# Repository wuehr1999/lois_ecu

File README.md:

# lois_ecu
This repository contains the [hardware](https://github.com/wuehr1999/lois_ecu/tree/main/hw), [firmware](https://github.com/wuehr1999/lois_ecu/tree/main/firmware) and [tooling](https://github.com/wuehr1999/lois_ecu/tree/main/rpmctrl_tuning) for a general purpose control unit for differential drive based wheeled robotics platforms. An image of the real hardware and a component diagram are shown below.

## Firmware

The [firmware](https://github.com/wuehr1999/lois_ecu/tree/main/firmware/loisECU) comes as a STM32 CubeIDE project and currently implements the following features:

- Closed single loop RPM-control for two DC-motors with encoders
- Realtime calculation of differential drive odometry
- Servo sweep for the [ball distribution device](https://github.com/generationmake/BDD)
- NMEA parser on RS232_1 (used for UBLOX GPS)
- NMEA parser on RS232_2 (used for KVH-C100 fluxgate compass)
- Host communication via UART
- 2048 Byte reealtime reord buffer ( recording of RPM, torque and compass heading over a given time )
- Easy human readable and debuggable ASCII communication leaned on modbus protocol with optional checksum

### Host communication protocol

The communication protocol is ASCII-based and the messages have the following format:

```:<8-bit command><32-bit payload><8-bit crc><\n>```

All values are written in hexadecimal, so that every message has a fixed length of 14 characters. There is also a [ROS2 driver](https://github.com/wuehr1999/lois_ecu_ros), which uses the given protocol to make the functionalities available via ROS.

The table below shows the currently implemented messages. There are also some periodic messages from the ECU to the Host. By writing the commands of this messages to the ECU, the period can be changed. The payload is then interpreted as an ```uint16``` containing the period time in milliseconds. ```0xfffe``` then means requesting a periodic message once and ```0xffff``` turns the message off completely.

| Command | Function | To ECU (E)/ To Host (H) | Payload interpretation | Periodic |
| - | - | - | - | - |
| ```0x01``` | Dutycycle of left and right motor, RPM controller gets disabled | E | ```2 x int16``` ( -100 % - 100 %)  | |
| ```0x02``` | RPM of left and right motor, RPM controller gets enabled | E | ```2 x int16``` | |
| ```0x03```  | Turn board LED on or off | E | ```bool``` | |
| ```0x04``` | Record a given amount of RPM samples | E / H | ```2 x uint16``` ( m samples left and n right ) to ECU or sequential max(m, n) ``` 2 x uint16``` ( tick timestamps in 100 ns followed by ```0x00000000``` ) to Host |  |
| ```0x05``` | Emergency stop button pressed | H | ```bool``` |  |
| ```0x06``` | Kp left controller | E | ```float32``` |  |
| ```0x07``` | Tn left controller | E | ```float32``` |  |
| ```0x08``` | Td left controller | E | ```float32``` |  |
| ```0x09``` | Kp right controller | E | ```float32``` |  |
| ```0x0a``` | Tn right controller | E | ```float32``` |  |
| ```0x0b``` | Td right controller | E | ```float32``` |  |
| ```0x0c``` | Record a given amount of compass heading samples | E | ```uint32```  n samples to ECU or sequential n + 1 ```2 x int16``` ( heading data in degrees ) followed by ```0x016A016A``` to Host |  |
| ```0x0d``` | GPS position | E / H | 3 sequential ```uint32, 2 x float32``` ( ```0xffffffff```, latitude, longitude ) | x |
| ```0x0e``` | GPS time | E / H | ```3 x uint8``` ( hours, minutes, seconds ) | x |
| ```0x0f``` | GPS date | E / H | ```3 x uint8``` ( year, month, day ) | x |
| ```0x10``` | Compass heading | E / H | ```1 x int16``` ( degrees to north ) | x |
| ```0x11``` | Terminal mode ( forward serial sensor Rx input on this interface ) | E | ```uint8``` ( Host protocol, GPS sensor, compass sensor ) | |
| ```0x12``` | Encoder overall ticks | E / H | 4 sequential ```4 x uint32``` ( ```0xffffffff```, timestamp in nanoseconds, left encoder, right encoder )  | x |
| ```0x13``` | Left encoder short level time correction | E | ```float32``` |  |
| ```0x14``` | Left encoder long level time correction | E | ```float32``` |  |
| ```0x15``` | Right encoder short level time correction | E | ```float32``` |  |
| ```0x16``` | Right encoder long level time correction | E | ```float32``` |  |
| ```0x17``` | Record a given amount of Torque samples | E / H | ```2 x uint16``` ( m samples left and n right ) to ECU or sequential max(m, n) ``` 2 x uint16``` ( torque 12-bit ADC values followed by ```0x00000000``` ) to Host |  |
| ```0x18``` | Reset all controllers, interfaces and counters | E  | - |  |
| ```0x19``` | Use ball distribution device once | E | - |  |
| ```0x20``` | Odometry calculated on robot | E / H | sequential 7 started with ```0xffffffff``` followed by ```6 x float32``` ( x, y, phi, dx, dy, dphi ) | x |

## Encoder and RPM controller tuning

There is [tooling in Scilab](https://github.com/wuehr1999/lois_ecu/tree/main/rpmctrl_tuning) provided, that can be used to find the parameters for the implemented RPM controller. The first step is recording a step response with full torque/ dutycycle and data of free spinning wheels at a constant dutycycle and  saving the data as ```*.csv``` files. This can for instance be done by using the ROS ecosystem of lois. There are also some examples in the controller tuning folder.

### Encoder correction

The ECU determines the RPM values of the robot by measuring the time of high and low levels of the encoder signals. With this implementation, also encoders with fewer steps ( usually mounted directly on the wheel ) can be used with a sufficient resolution. The problem is, that some encoders have inequal high and low times. Therefore [correction factors](https://github.com/wuehr1999/lois_ecu/blob/main/rpmctrl_tuning/edgecorrect/correct.sce) can be calculated and entered at runtime ( commands ```0x13 - 0x16``` ) from the free spinning record.

### Finding the controller parameters

The controller is updated in the ECU with a frequency of ```5 Hz```. It is only a single loop RPM controller without a cascade for torque control, as it is not necessary for most differential drivetrain applications.

There is one band limited PI controller for each motor with the transfer function ```G(s) = Kp * ( 1 + s * Tn ) / ( s * Tn * ( 1 + s * Td ))```.

The Scilab tooling helps to [approximate the plant from the step response as 1st or 2nd order system and find sufficient controller settings](https://github.com/wuehr1999/lois_ecu/blob/main/rpmctrl_tuning/stepresponse/main.sce). The tuning paradigm is the compensation of the most critical pole of the plant followed by gain optimization. The following [goal parameters](https://github.com/wuehr1999/lois_ecu/blob/main/rpmctrl_tuning/stepresponse/init.sce) that can be selected:
- Encoder steps per revolution
- Controller frequency in Hz
- Don't optimize for phase margin with gain optimum ( ```Td = 0``` )
- Maximum overshoot inpercent
- Step response destination in % for optimization ( average RPM value during operation )
- Stabilization time in seconds
- Tolerance band in %

## PCB toplayer

## PCB bottomlayer

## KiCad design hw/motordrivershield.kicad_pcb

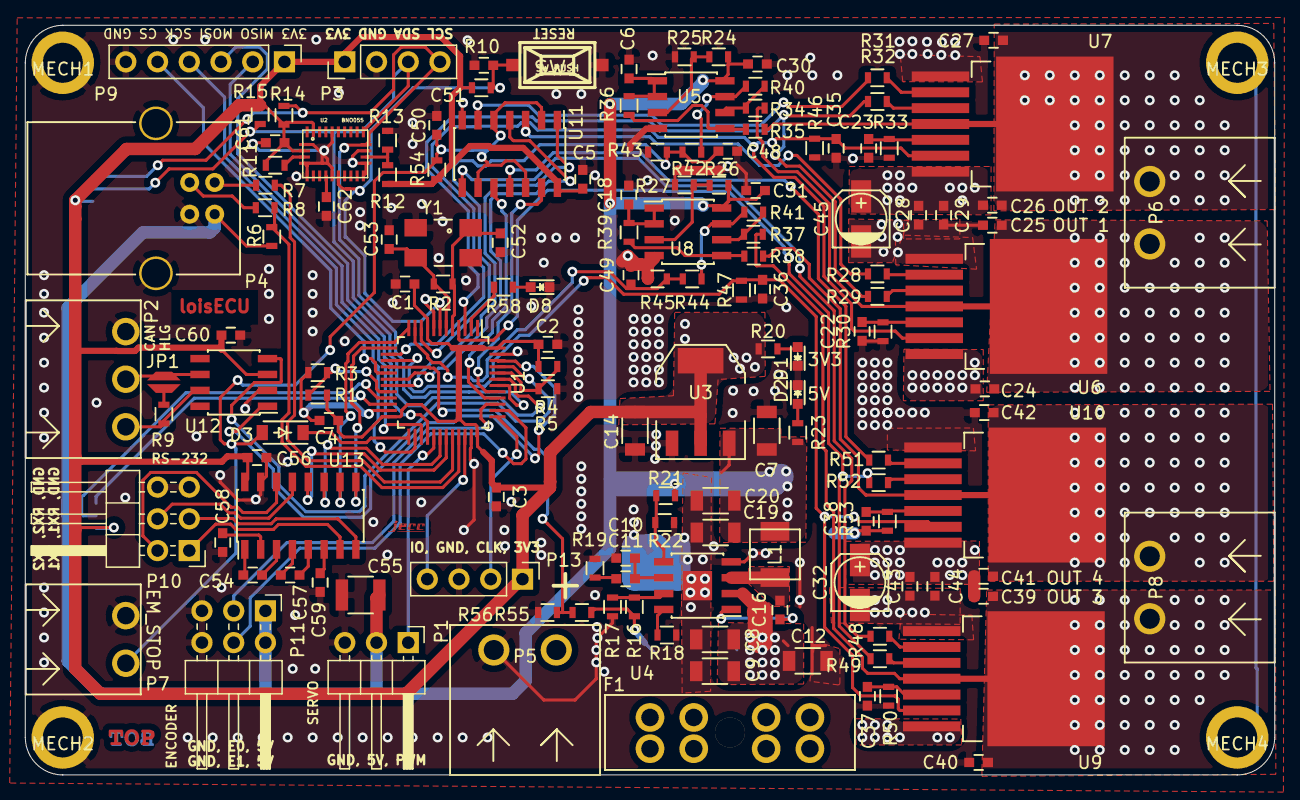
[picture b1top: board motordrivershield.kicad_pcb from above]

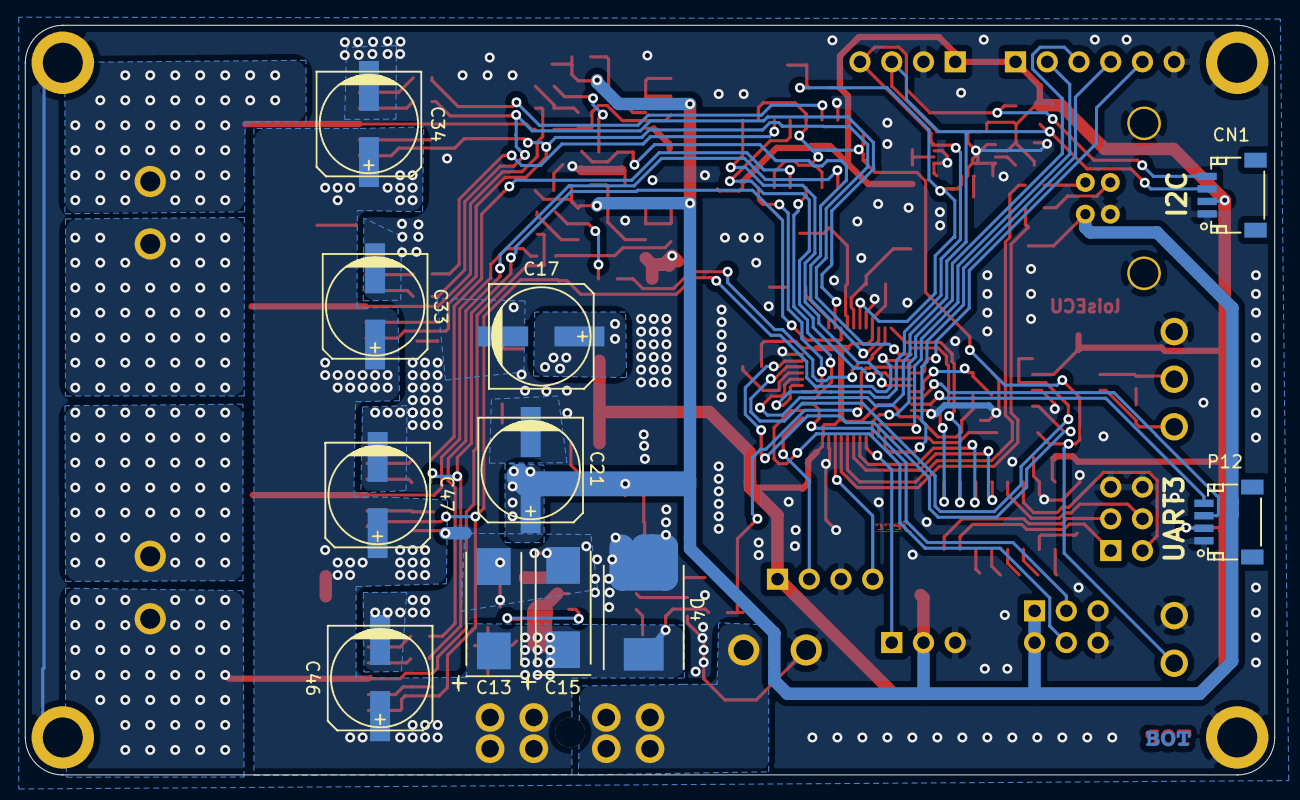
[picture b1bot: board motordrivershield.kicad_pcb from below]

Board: 2 copper layers, 100.0 x 60.0 mm, 163 parts (11 on the bottom side), 103 nets.

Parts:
C1, C2, C3, C4, C5, C6, C16, C18, C22, C23, C28, C29, C30, C31, C37, C38, C43, C44, C50, C51, C54, C56, C57, C58, C59, C60, C61, C62: 100nF; C_0603
C7: 10uF; C_1206
C8, C9: 4.7uF 50V; C_1206
C10: 120pF; C_0603
C11: 12nF; C_0603
C12: 100nF; C_1206
C13, C15: 47uF; TantalC_SizeD_EIA-7343_Wave
C14, C19, C20: 22uF; C_1206
C17, C21: 47uF; c_elec_8x6.7
C24, C25, C26, C27, C39, C40, C41, C42: 220nF; C_0603
C32, C45: DNI; c_elec_4x4.5
C33, C34, C46, C47: DNI; c_elec_8x6.7
C35, C36, C48, C49: 1nF; C_0603
C52, C53: 20pF; C_0603
C55: 10uF; C_1210
CN1: QWIIC; Connectors_JST_SM04B-SRSS-TB
D1, D2, D8: Led_Small; LED_0603
D3: BAT46W; SOD-123
D4: D_Small; DO-214AB
F1: 15A; Fuseholder_ATO_Blade_littlefuse_8_Pin
JP1: Jumper_NC_Small; SolderJumper_2mm
L1: 74437324150; WE-LHMI40xx
L2: Label; jecc_logo
L3: Label; Top
L4: Label; Bot
MECH1, MECH2, MECH3, MECH4: MHP_3.2_5.0
P1: CONN_01X03; PinHeader_1x03_P2.54mm_Horizontal
P2: CONN_01X03; WR-TBL_691322310003
P3, P13: CONN_01X04; PinHeader_1x04_P2.54mm_Vertical
P4: USB_B
P5, P6, P8: WR-TBL_691313710002
P7: CONN_01X02; WR-TBL_691322310002
P9: CONN_01X06; PinHeader_1x06_P2.54mm_Vertical
P10, P11: CONN_02X03; PinHeader_2x03_P2.54mm_Horizontal
P12: CONN_01X04; Connectors_JST_SM04B-SRSS-TB
R1, R3, R4, R5, R21: 100k; R_0603
R2: 1M; R_0603
R6: 4k7; R_0603
R7, R8: 20; R_0603
R9: 120; R_0603
R10, R11, R14, R15, R24, R26, R28, R29, R31, R32, R42, R44, R48, R49, R51, R52, R54, R56: 10k; R_0603
R12, R13: 0R0; R_0603
R16: 220k; R_0603
R17: 43.2k; R_0603
R18: 143k; R_0603
R19: 3.74k; R_0603
R20, R23: 220; R_0603
R22: 19.1k; R_0603
R25, R27: 5.6k; R_0603
R30, R33, R50, R53: 510; R_0603
R34, R35, R37, R38: 56k; R_0603
R36, R39, R40, R41, R43, R45: 22k; R_0603
R46, R47, R58: 1k; R_0603
R55: 150k; R_0603
SW1: SW_PUSH; smd_push
U1: STM32F103C8Tx; LQFP-48_7x7mm_Pitch0.5mm
U2: BNO055; LGA-28-5832
U3: LT1117; SOT-223
U4: TPS54335A; SOIC-8-1EP_3.9x4.9mm_Pitch1.27mm
U5, U8: LM358; SOIC-8_3.9x4.9mm_Pitch1.27mm
U6, U7, U9, U10: IFX007T; TO-263-7Lead
U11: 74xx32; SOIC-14_3.9x8.7mm_Pitch1.27mm
U12: SN65HVD232; SOIC-8_3.9x4.9mm_Pitch1.27mm
U13: MAX3232; SOIC-16_3.9x9.9mm_Pitch1.27mm
Y1: 16M; Crystal_SMD_0603_4Pads

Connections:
+3V3: C1.1, C2.1, C3.1, C4.1, C5.1, C14.1, C17.1, C56.1, C60.1, C61.1, CN1.2, P3.1, P9.1, P12.2, P13.1, R1.1, R4.1, R10.1, R11.1, R12.1, R14.1, R15.1, R20.1, R54.1, U1.9, U1.24, U1.36, U1.48, U2.3, U2.28, U3.2, U3.4, U11.14, U12.3, U13.16
+5V: C7.1, C19.1, C20.1, C21.1, C30.2, C31.2, C55.1, L1.2, P1.2, P4.1, P11.1, P11.2, R6.1, R21.1, R23.1, R24.1, R26.1, U3.3, U5.8, U8.8
+BATT: C8.1, C9.1, C12.1, C13.1, C15.1, C24.1, C26.1, C28.1, C29.1, C32.1, C33.1, C34.1, C39.1, C41.1, C43.1, C44.1, C45.1, C46.1, C47.1, D4.1, F1.2, R16.1, R55.1, U4.2, U6.7, U7.7, U9.7, U10.7
/interfaces/nCANH: P2.3, R9.2, U12.7
/interfaces/nCANL: JP1.2, P2.2, U12.6
/interfaces/nRX1: P10.4, U13.13
/interfaces/nRX2: P10.3, U13.8
/interfaces/nTX1: P10.2, U13.14
/interfaces/nTX2: P10.1, U13.7
/power/COMP: C10.1, C11.1, U4.6
/power/EN: R16.2, R17.1, U4.7
/power/PH: C16.1, L1.1, U4.3
/power/RT: R18.1, U4.8
/power/SENSE5V: R21.2, R22.1, U4.5
/powertrain/EM_S: C50.1, D3.2, P7.2, R54.2, U11.2, U11.5, U11.9, U11.12
/powertrain/IN1: R28.2, U11.3
/powertrain/IN2: R31.2, U11.6
/powertrain/IN3: R48.2, U11.8
/powertrain/IN4: R51.2, U11.11
/powertrain/OUT1: C24.2, C25.1, P6.1, R34.2, U6.4, U6.8
/powertrain/OUT2: C26.2, C27.1, P6.2, R35.2, U7.4, U7.8
/powertrain/OUT3: C39.2, C40.1, P8.1, R37.2, U9.4, U9.8
/powertrain/OUT4: C41.2, C42.1, P8.2, R38.2, U10.4, U10.8
BEMF12: C48.1, R42.2, R43.1, U1.10
BEMF34: C49.1, R44.2, R45.1, U1.11
BOOT0: R4.2, R5.1, U1.44
BOOT1: R1.2, R3.1, U1.20
CAN_RX: U1.45, U12.4
CAN_TX: U1.46, U12.1
CS: P9.5, U1.17
EM_STOP: D3.1, U1.25
ENCODER0: P11.3, U1.39
ENCODER1: P11.4, U1.38
GND: C1.2, C2.2, C3.2, C4.2, C5.2, C6.2, C7.2, C8.2, C9.2, C10.2, C12.2, C13.2, C14.2, C15.2, C17.2, C18.2, C19.2, C20.2, C21.2, C22.2, C23.2, C25.2, C27.2, C28.2, C29.2, C30.1, C31.1, C32.2, C33.2, C34.2, C35.2, C36.2, C37.2, C38.2, C40.2, C42.2, C43.2, C44.2, C45.2, C46.2, C47.2, C48.2, C49.2, C50.2, C51.2, C52.2, C53.2, C55.2, C56.2, C58.1, C59.2, C60.2, C61.2, C62.2, CN1.1, D1.1, D2.1, D4.2, D8.1, MECH1.1, MECH2.1, MECH3.1, MECH4.1, P1.3, P2.1, P3.2, P4.4, P4.5, P5.1, P7.1, P9.6, P10.5, P10.6, P11.5, P11.6, P12.1, P13.3, R3.2, R5.2, R13.2, R17.2, R18.2, R19.2, R22.2, R25.2, R27.2, R30.2, R33.2, R43.2, R45.2, R46.2, R47.2, R50.2, R53.2, R56.2, SW1.2, U1.8, U1.23, U1.35, U1.47, U2.2, U2.5, U2.6, U2.10, U2.15, U2.16, U2.18, U2.25, U3.1, U4.4, U4.9, U5.4, U6.1, U7.1, U8.4, U9.1, U10.1, U11.7, U12.2, U13.15, Y1.2, Y1.4
INH12: R29.2, R32.2, U1.3
INH34: R49.2, R52.2, U1.4
IS12: C35.1, R46.1, U1.14, U6.6, U7.6
IS34: C36.1, R47.1, U1.15, U9.6, U10.6
MISO2: P9.2, U1.27
MOSI2: P9.3, U1.28
unnamed: C6.1, R36.2, U5.1, U5.2
unnamed: C11.2, R19.1
unnamed: C16.2, U4.1
unnamed: C18.1, R39.2, U8.1, U8.2
unnamed: C22.1, R30.1, U6.5
unnamed: C23.1, R33.1, U7.5
unnamed: C37.1, R50.1, U9.5
unnamed: C38.1, R53.1, U10.5
unnamed: C54.1, U13.1
unnamed: C54.2, U13.3
unnamed: C57.1, U13.4
unnamed: C57.2, U13.5
unnamed: C58.2, U13.2
unnamed: C59.1, U13.6
unnamed: C62.1, U2.9
unnamed: D1.2, R20.2
unnamed: D2.2, R23.2
unnamed: D8.2, R58.1
unnamed: F1.1, P5.2
unnamed: JP1.1, R9.1
unnamed: P4.2, R7.1
unnamed: P4.3, R8.1
unnamed: R11.2, U2.4
unnamed: R12.2, R13.1, U2.17
unnamed: R24.2, R25.1, U5.3
unnamed: R26.2, R27.1, U8.3
unnamed: R28.1, U6.2
unnamed: R29.1, U6.3
unnamed: R31.1, U7.2
unnamed: R32.1, U7.3
unnamed: R34.1, R40.2, U5.6
unnamed: R35.1, R36.1, U5.5
unnamed: R37.1, R41.2, U8.6
unnamed: R38.1, R39.1, U8.5
unnamed: R40.1, R42.1, U5.7
unnamed: R41.1, R44.1, U8.7
unnamed: R48.1, U9.2
unnamed: R49.1, U9.3
unnamed: R51.1, U10.2
unnamed: R52.1, U10.3
unnamed: R58.2, U1.2
OSC_IN: C52.1, R2.2, U1.5, Y1.1
OSC_OUT: C53.1, R2.1, U1.6, Y1.3
PWM1: U1.19, U11.1
PWM2: U1.18, U11.4
PWM3: U1.40, U11.10
PWM4: U1.41, U11.13
RESET: C51.1, R10.2, SW1.1, U1.7, U2.11
RX1: U1.31, U13.12
RX2: U1.13, U13.9
RX3: P12.4, U1.22
SCK2: P9.4, U1.26
SCL1: CN1.4, P3.4, R14.2, U1.42, U2.19
SDA1: CN1.3, P3.3, R15.2, U1.43, U2.20
SERVO: P1.1, U1.29
SWCLK: P13.2, U1.37
SWDIO: P13.4, U1.34
TX1: U1.30, U13.11
TX2: U1.12, U13.10
TX3: P12.3, U1.21
USB+: R6.2, R8.2, U1.33
USB-: R7.2, U1.32
VIN_MEAS: R55.2, R56.1, U1.16

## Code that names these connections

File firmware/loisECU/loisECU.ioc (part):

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Mcu.UserName=STM32F103C8Tx
PB10.Mode=Asynchronous
PC13-TAMPER-RTC.GPIOParameters=GPIO_Label
PA6.GPIO_Label=BATSENSE
PB0.GPIO_Label=PWM2
PB6.GPIO_Label=SCL
PB3.GPIO_ModeDefaultEXTI=GPIO_MODE_IT_RISING_FALLING
PB11.Signal=USART3_RX
PC15-OSC32_OUT.GPIO_Label=INH34
RCC.SYSCLKSource=RCC_SYSCLKSOURCE_PLLCLK
PB5.GPIOParameters=GPIO_Label
PD1-OSC_OUT.Signal=RCC_OSC_OUT
PA15.GPIO_Label=ENCODER1
PB4.GPIOParameters=GPIO_Label
PA15.GPIO_ModeDefaultEXTI=GPIO_MODE_IT_RISING_FALLING
PB6.Signal=GPIO_Output
PA8.GPIOParameters=GPIO_Label
PA0-WKUP.GPIOParameters=GPIO_Label
PB12.GPIO_Label=EMSTOP
PB0.GPIOParameters=GPIO_Label
PB3.GPIO_PuPd=GPIO_NOPULL
PA1.GPIOParameters=GPIO_Label
PA14.Mode=Serial_Wire
PB1.GPIO_Label=PWM1
PB3.GPIOParameters=GPIO_PuPd,GPIO_Label,GPIO_ModeDefaultEXTI
PB7.Signal=GPIO_Output
PA8.Signal=S_TIM1_CH1
PB6.GPIOParameters=GPIO_Label
PC14-OSC32_IN.GPIOParameters=GPIO_Label
PB7.GPIO_Label=SDA
Mcu.Package=LQFP48
PB1.Signal=S_TIM3_CH4
PA6.Signal=ADCx_IN6
PA10.Signal=USART1_RX
PA15.Signal=GPXTI15
PA5.GPIOParameters=GPIO_Label
PB5.GPIO_Label=PWM4
PC14-OSC32_IN.GPIO_Label=INH12
PC15-OSC32_OUT.GPIOParameters=GPIO_Label
PA4.GPIO_Label=IS12
PB4.Signal=S_TIM3_CH1
PA3.Signal=USART2_RX
PB3.GPIO_Label=ENCODER0
PA6.GPIOParameters=GPIO_Label
PD1-OSC_OUT.Mode=HSE-External-Oscillator
PA10.Mode=Asynchronous
PA15.GPIOParameters=GPIO_PuPd,GPIO_Label,GPIO_ModeDefaultEXTI
PC13-TAMPER-RTC.Signal=GPIO_Output
PD0-OSC_IN.Signal=RCC_OSC_IN
PC14-OSC32_IN.Signal=GPIO_Output
PA0-WKUP.GPIO_Label=BEMF12
PA0-WKUP.Signal=ADCx_IN0
PA3.Mode=Asynchronous
PA13.Signal=SYS_JTMS-SWDIO
PA9.Mode=Asynchronous
PA8.GPIO_Label=SERVO
PB11.Mode=Asynchronous
PB7.GPIOParameters=GPIO_Label
PA9.Signal=USART1_TX
PC15-OSC32_OUT.Signal=GPIO_Output
PA1.Signal=ADCx_IN1
PD0-OSC_IN.Mode=HSE-External-Oscillator
PB10.Signal=USART3_TX
PA5.Signal=ADCx_IN5
board=custom
PC13-TAMPER-RTC.GPIO_Label=LED
PB4.GPIO_Label=PWM3
PA1.GPIO_Label=BEMF34
PA4.GPIOParameters=GPIO_Label
PA13.Mode=Serial_Wire
Mcu.Name=STM32F103C(8-B)Tx
PA2.Signal=USART2_TX
PB3.Signal=GPXTI3
PA4.Signal=ADCx_IN4
RCC.SYSCLKFreq_VALUE=72000000
PB5.Signal=S_TIM3_CH2
PA7.GPIO_Label=CS
PA5.GPIO_Label=IS34
PA11.Signal=USB_DM
PA14.Signal=SYS_JTCK-SWCLK
PB12.GPIO_ModeDefaultEXTI=GPIO_MODE_IT_RISING_FALLING
PA15.GPIO_PuPd=GPIO_NOPULL
PA2.Mode=Asynchronous
PB12.GPIO_PuPd=GPIO_NOPULL
PB0.Signal=S_TIM3_CH3
PA7.GPIOParameters=GPIO_Label
PB12.GPIOParameters=GPIO_PuPd,GPIO_Label,GPIO_ModeDefaultEXTI
PB12.Signal=GPXTI12
PB1.GPIOParameters=GPIO_Label
PA7.Signal=GPIO_Output

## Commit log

2022-12-25 software
2022-12-25 umlet diagram
2022-12-25 readme update
2022-12-28 firmware update
2022-12-28 firmware fix
2023-02-15 precontrol, reenable gps parsing
2023-02-16 fix feed forward and jerk limiting
